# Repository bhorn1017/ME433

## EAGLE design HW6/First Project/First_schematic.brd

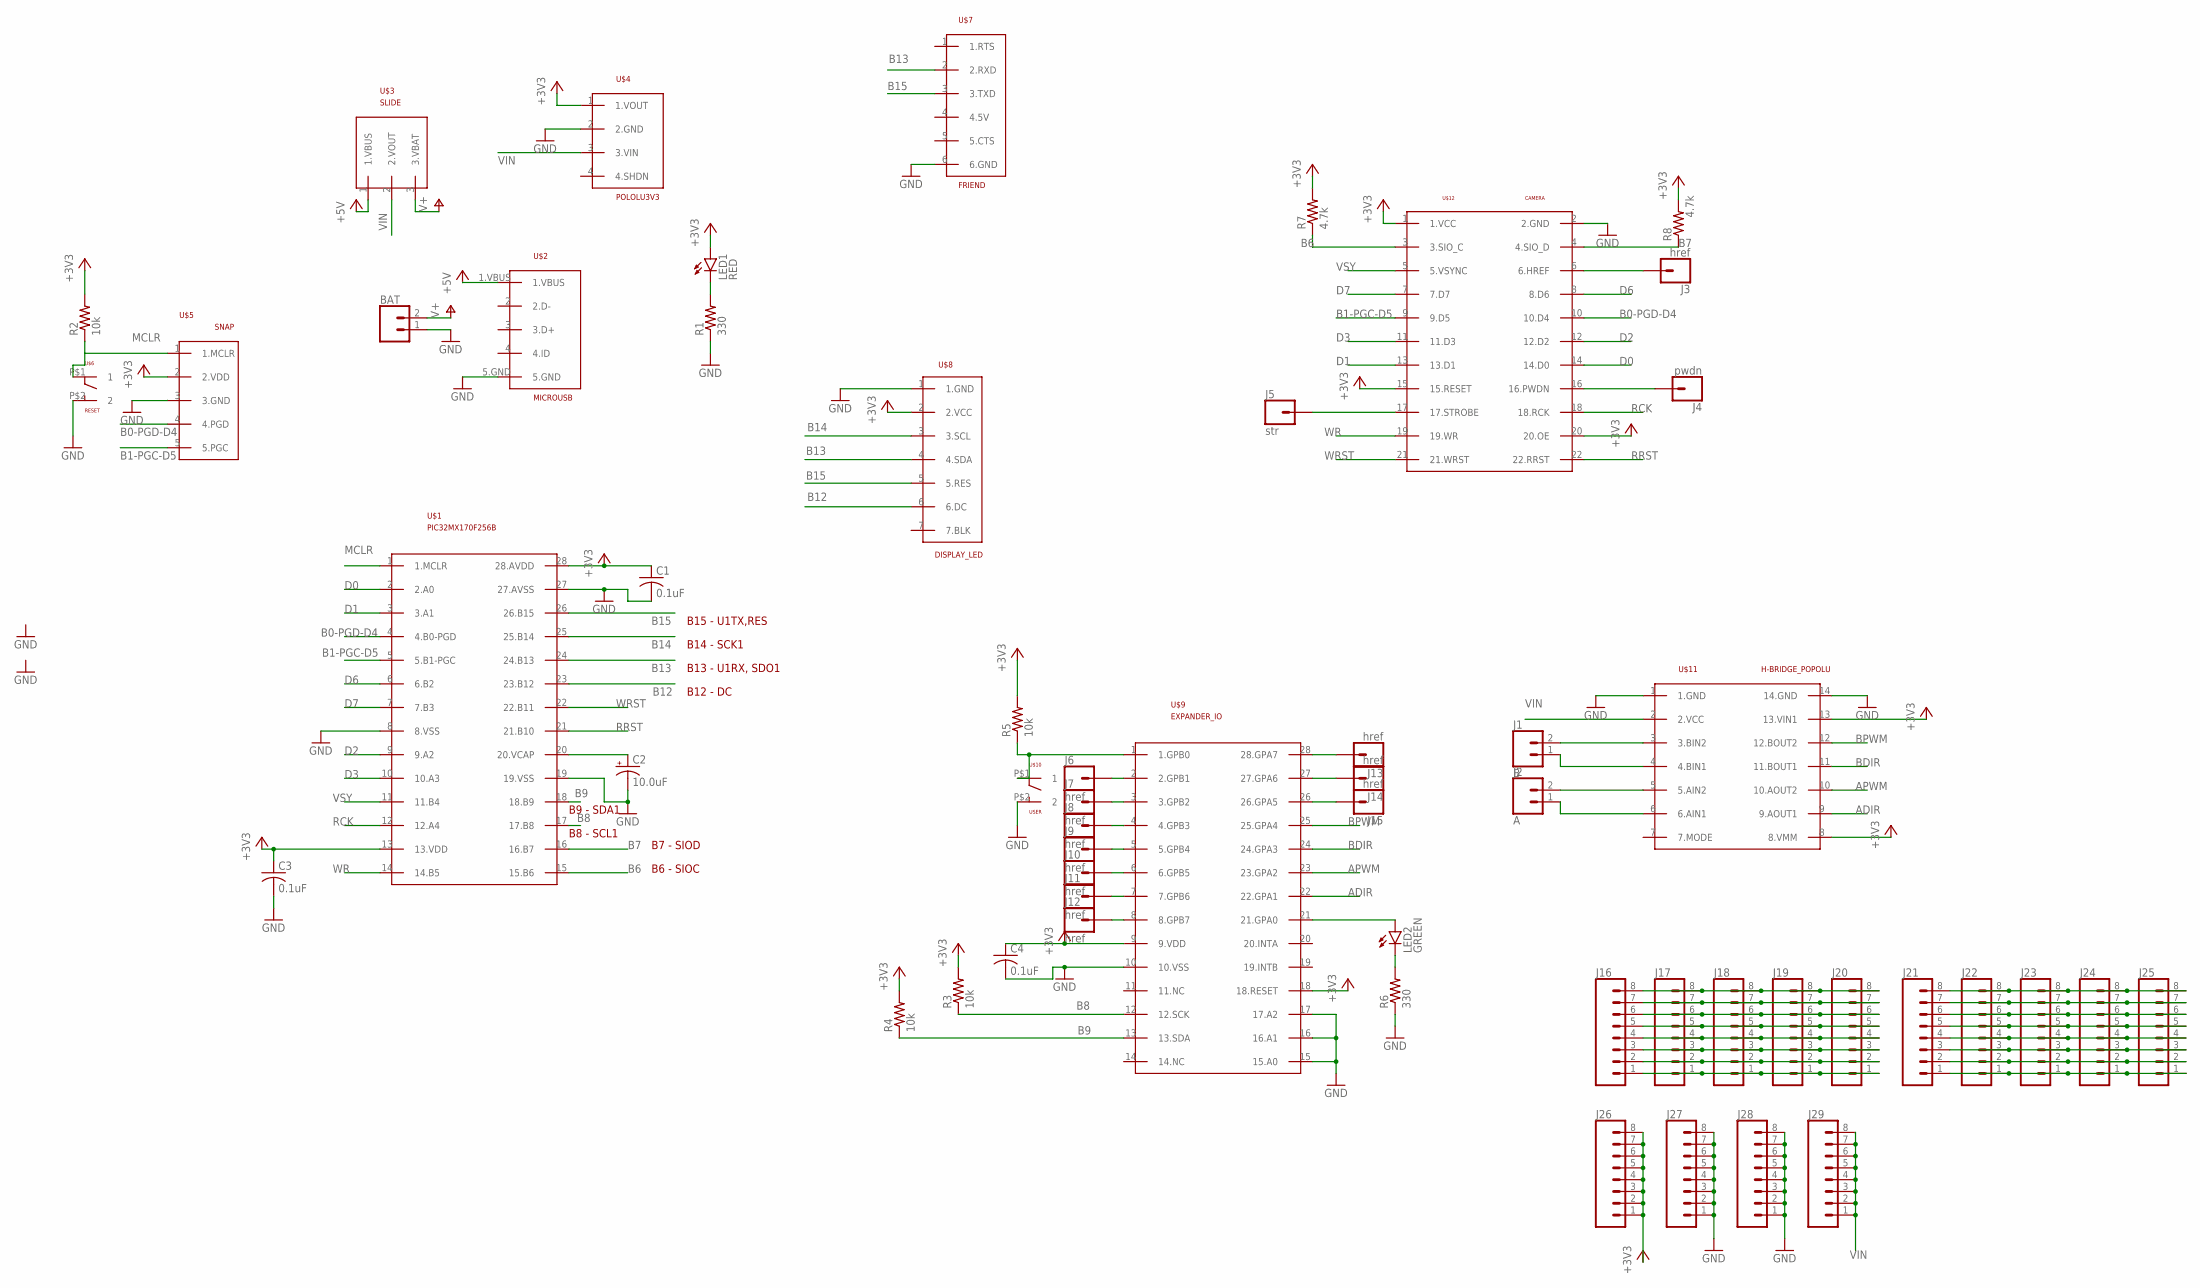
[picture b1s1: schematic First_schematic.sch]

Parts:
BAT: CONN_02; 1X02
C1, C3, C4: 0.1uF; C025-030X050
C2: 10.0uF; B45181B
J1: B; 1X02
J2: A; 1X02
J3, J6, J7, J8, J9, J10, J11, J12, J13, J14, J15: href; 1X01
J4: pwdn; 1X01
J5: str; 1X01
J16, J17, J18, J19, J20, J21, J22, J23, J24, J25, J26, J27, J28, J29: CONN_08"; 1X08
LED1: RED; LED3MM
LED2: GREEN; LED3MM
R1, R6: 330; 0207/10
R2, R3, R4, R5: 10k; 0207/10
R7, R8: 4.7k; 0207/10
U$1: PIC32MX170F256B; DIL28-3
U$2: MICROUSB
U$3: SLIDE
U$4: POLOLU3V3
U$5: SNAP; 1X05
U$6: RESET; PUSH
U$7: FRIEND
U$8: DISPLAY_LED
U$9: EXPANDER_IO; DIL28-3
U$10: USER; PUSH
U$11: H-BRIDGE_POPOLU; H-BRIDGE_POLOLU
U$12: CAMERA; CAMERA_REAL_SIZE

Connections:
+3V3: C1.1, C3.1, C4.1, J26.1, J26.2, J26.3, J26.4, J26.5, J26.6, J26.7, J26.8, LED1.A, R2.2, R3.2, R4.2, R5.2, R7.2, R8.2, U$1.13 (13.VDD), U$1.28 (28.AVDD), U$4.1 (1.VOUT), U$5.2 (2.VDD), U$8.2 (2.VCC), U$9.9 (9.VDD), U$9.18 (18.RESET), U$11.8 (8.VMM), U$11.13 (13.VIN1), U$12.1 (1.VCC), U$12.15 (15.RESET), U$12.20 (20.OE)
+5V: U$2.1.VBUS, U$3.1 (1.VBUS)
ADIR: U$9.22 (22.GPA1), U$11.9 (9.AOUT1)
APWM: U$9.23 (23.GPA2), U$11.10 (10.AOUT2)
B0-PGD-D4: U$1.4 (4.B0-PGD), U$5.4 (4.PGD), U$12.10 (10.D4)
B1-PGC-D5: U$1.5 (5.B1-PGC), U$5.5 (5.PGC), U$12.9 (9.D5)
B6: R7.1, U$1.15 (15.B6), U$12.3 (3.SIO_C)
B7: R8.1, U$1.16 (16.B7), U$12.4 (4.SIO_D)
B8: R3.1, U$1.17 (17.B8), U$9.12 (12.SCK)
B9: R4.1, U$1.18 (18.B9), U$9.13 (13.SDA)
B12: U$1.23 (23.B12), U$8.6 (6.DC)
B13: U$1.24 (24.B13), U$7.2 (2.RXD), U$8.4 (4.SDA)
B14: U$1.25 (25.B14), U$8.3 (3.SCL)
B15: U$1.26 (26.B15), U$7.3 (3.TXD), U$8.5 (5.RES)
BDIR: U$9.24 (24.GPA3), U$11.11 (11.BOUT1)
BPWM: U$9.25 (25.GPA4), U$11.12 (12.BOUT2)
D0: U$1.2 (2.A0), U$12.14 (14.D0)
D1: U$1.3 (3.A1), U$12.13 (13.D1)
D2: U$1.9 (9.A2), U$12.12 (12.D2)
D3: U$1.10 (10.A3), U$12.11 (11.D3)
D6: U$1.6 (6.B2), U$12.8 (8.D6)
D7: U$1.7 (7.B3), U$12.7 (7.D7)
GND: BAT.1, C1.2, C2.-, C3.2, C4.2, J27.1, J27.2, J27.3, J27.4, J27.5, J27.6, J27.7, J27.8, J28.1, J28.2, J28.3, J28.4, J28.5, J28.6, J28.7, J28.8, R1.1, R6.1, U$1.8 (8.VSS), U$1.19 (19.VSS), U$1.27 (27.AVSS), U$2.5.GND, U$4.2 (2.GND), U$5.3 (3.GND), U$6.P$2 (2), U$7.6 (6.GND), U$8.1 (1.GND), U$9.10 (10.VSS), U$9.15 (15.A0), U$9.16 (16.A1), U$9.17 (17.A2), U$10.P$2 (2), U$11.1 (1.GND), U$11.14 (14.GND), U$12.2 (2.GND)
MCLR: U$1.1 (1.MCLR), U$5.1 (1.MCLR)
unnamed: LED1.K (C), R1.2
unnamed: R2.1, U$6.P$1 (1)
unnamed: C2.+, U$1.20 (20.VCAP)
unnamed: LED2.A, U$9.21 (21.GPA0)
unnamed: LED2.K (C), R6.2
unnamed: R5.1, U$9.1 (1.GPB0), U$10.P$1 (1)
unnamed: J1.2, U$11.3 (3.BIN2)
unnamed: J1.1, U$11.4 (4.BIN1)
unnamed: J2.2, U$11.5 (5.AIN2)
unnamed: J2.1, U$11.6 (6.AIN1)
unnamed: J3.1, U$12.6 (6.HREF)
unnamed: J4.1, U$12.16 (16.PWDN)
unnamed: J5.1, U$12.17 (17.STROBE)
unnamed: J6.1, U$9.2 (2.GPB1)
unnamed: J7.1, U$9.3 (3.GPB2)
unnamed: J8.1, U$9.4 (4.GPB3)
unnamed: J9.1, U$9.5 (5.GPB4)
unnamed: J10.1, U$9.6 (6.GPB5)
unnamed: J11.1, U$9.7 (7.GPB6)
unnamed: J12.1, U$9.8 (8.GPB7)
unnamed: J15.1, U$9.26 (26.GPA5)
unnamed: J14.1, U$9.27 (27.GPA6)
unnamed: J13.1, U$9.28 (28.GPA7)
unnamed: J16.8, J17.8, J18.8, J19.8, J20.8
unnamed: J16.7, J17.7, J18.7, J19.7, J20.7
unnamed: J16.6, J17.6, J18.6, J19.6, J20.6
unnamed: J16.5, J17.5, J18.5, J19.5, J20.5
unnamed: J16.4, J17.4, J18.4, J19.4, J20.4
unnamed: J16.3, J17.3, J18.3, J19.3, J20.3
unnamed: J16.2, J17.2, J18.2, J19.2, J20.2
unnamed: J16.1, J17.1, J18.1, J19.1, J20.1
unnamed: J21.8, J22.8, J23.8, J24.8, J25.8
unnamed: J21.7, J22.7, J23.7, J24.7, J25.7
unnamed: J21.6, J22.6, J23.6, J24.6, J25.6
unnamed: J21.5, J22.5, J23.5, J24.5, J25.5
unnamed: J21.4, J22.4, J23.4, J24.4, J25.4
unnamed: J21.3, J22.3, J23.3, J24.3, J25.3
unnamed: J21.2, J22.2, J23.2, J24.2, J25.2
unnamed: J21.1, J22.1, J23.1, J24.1, J25.1
RCK: U$1.12 (12.A4), U$12.18 (18.RCK)
RRST: U$1.21 (21.B10), U$12.22 (22.RRST)
V+: BAT.2, U$3.3 (3.VBAT)
VIN: J29.1, J29.2, J29.3, J29.4, J29.5, J29.6, J29.7, J29.8, U$3.2 (2.VOUT), U$4.3 (3.VIN), U$11.2 (2.VCC)
VSY: U$1.11 (11.B4), U$12.5 (5.VSYNC)
WR: U$1.14 (14.B5), U$12.19 (19.WR)
WRST: U$1.22 (22.B11), U$12.21 (21.WRST)

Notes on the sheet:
B14 - SCK1
B12 - DC
B13 - U1RX, SDO1
B15 - U1TX,RES
B9 - SDA1
B8 - SCL1
B7 - SIOD
B6 - SIOC

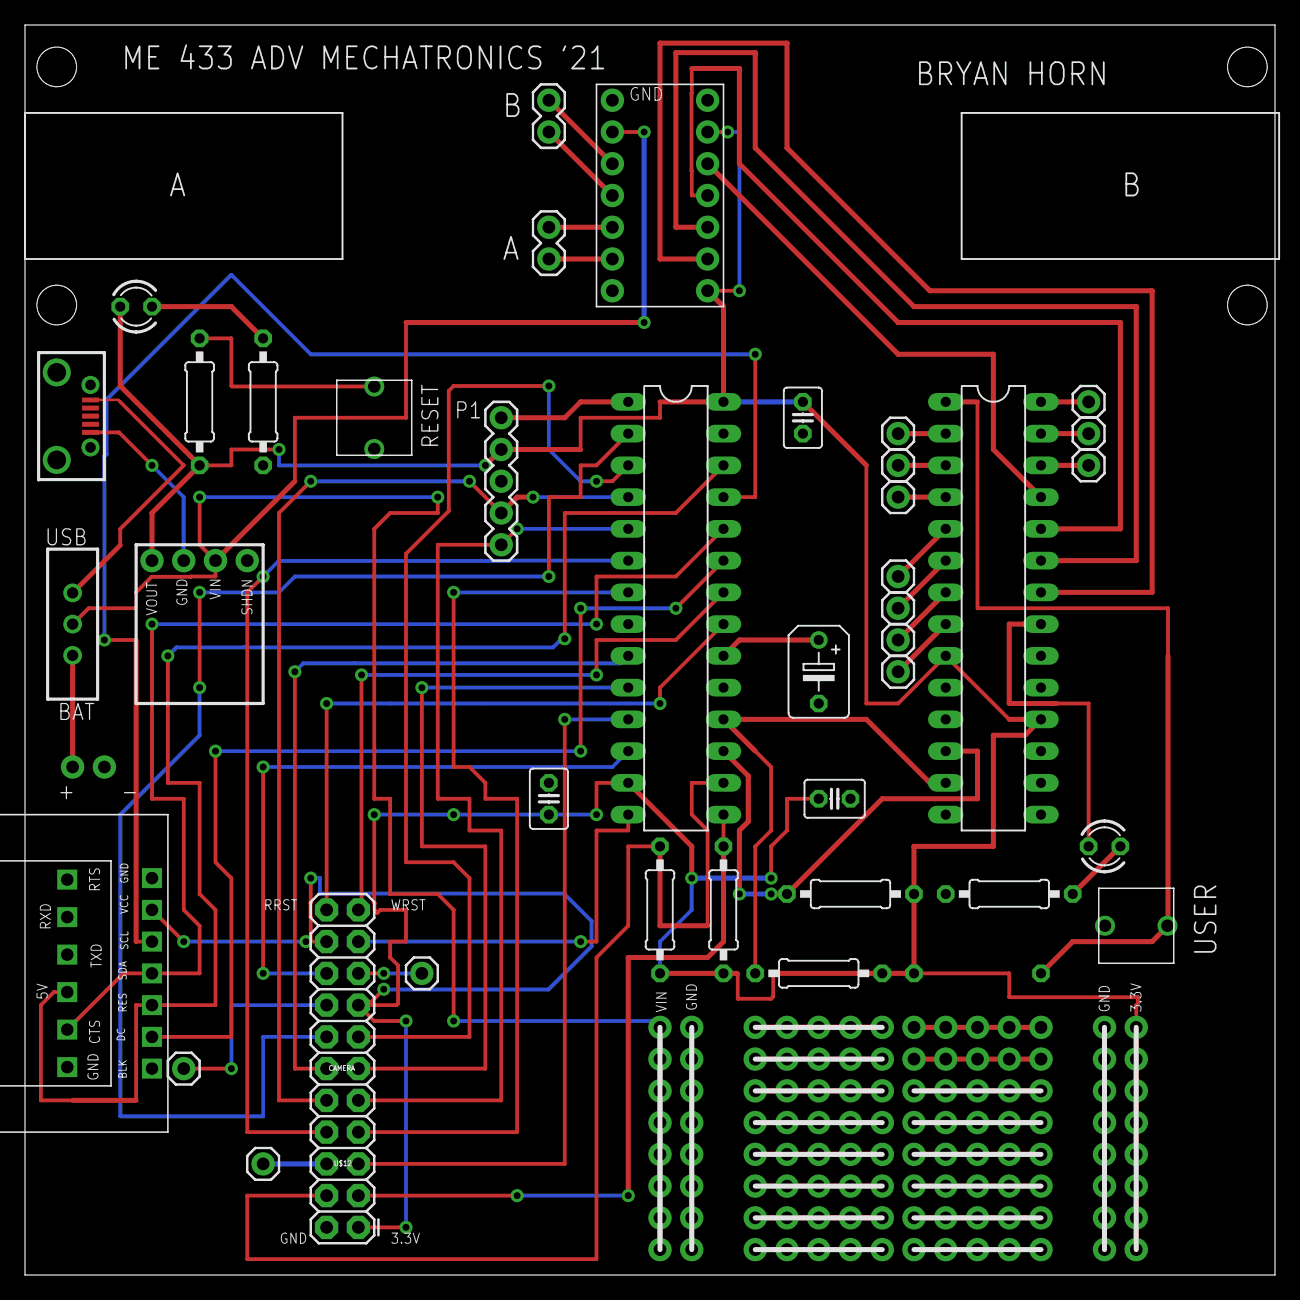
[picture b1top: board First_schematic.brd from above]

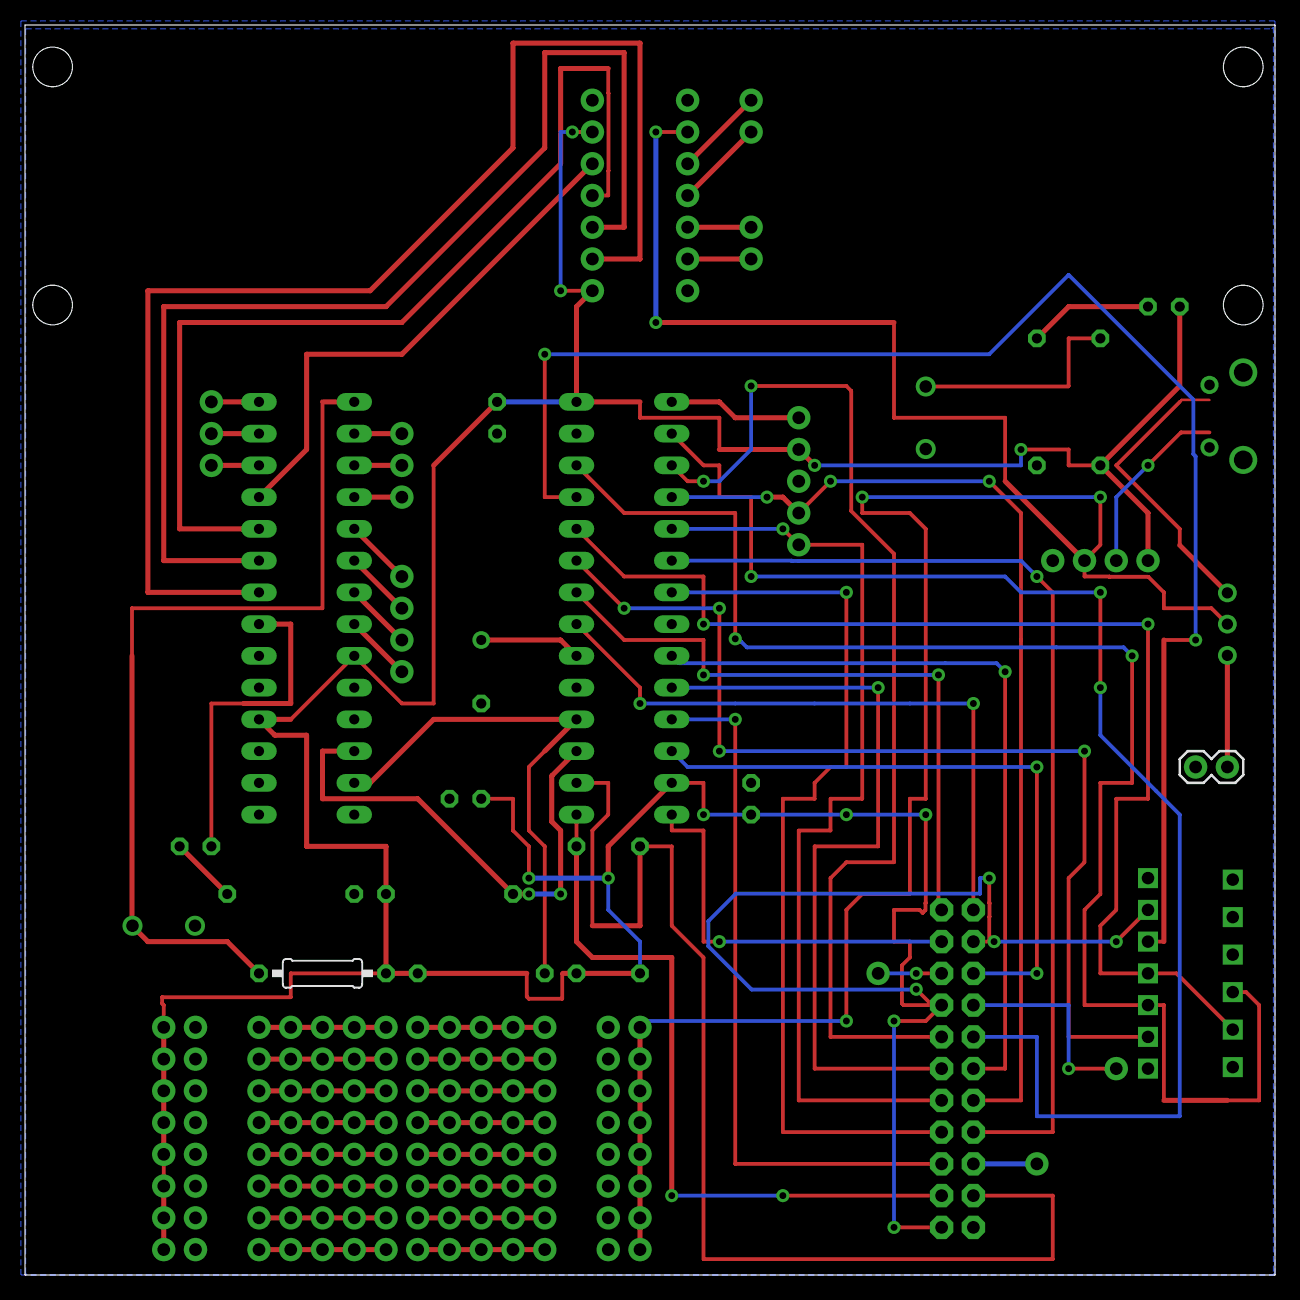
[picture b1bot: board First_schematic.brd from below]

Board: 2 copper layers, 100.0 x 100.0 mm, 56 parts (3 on the bottom side), 70 nets.

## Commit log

2021-04-09 HW2 Attempt
2021-04-09 Lab Kit Pic
2021-04-30 HW10
2021-05-10 HW9 edits
2021-05-10 HW11
2021-05-10 HW 11 Edits
    Added FPS
2021-06-10 HW14
